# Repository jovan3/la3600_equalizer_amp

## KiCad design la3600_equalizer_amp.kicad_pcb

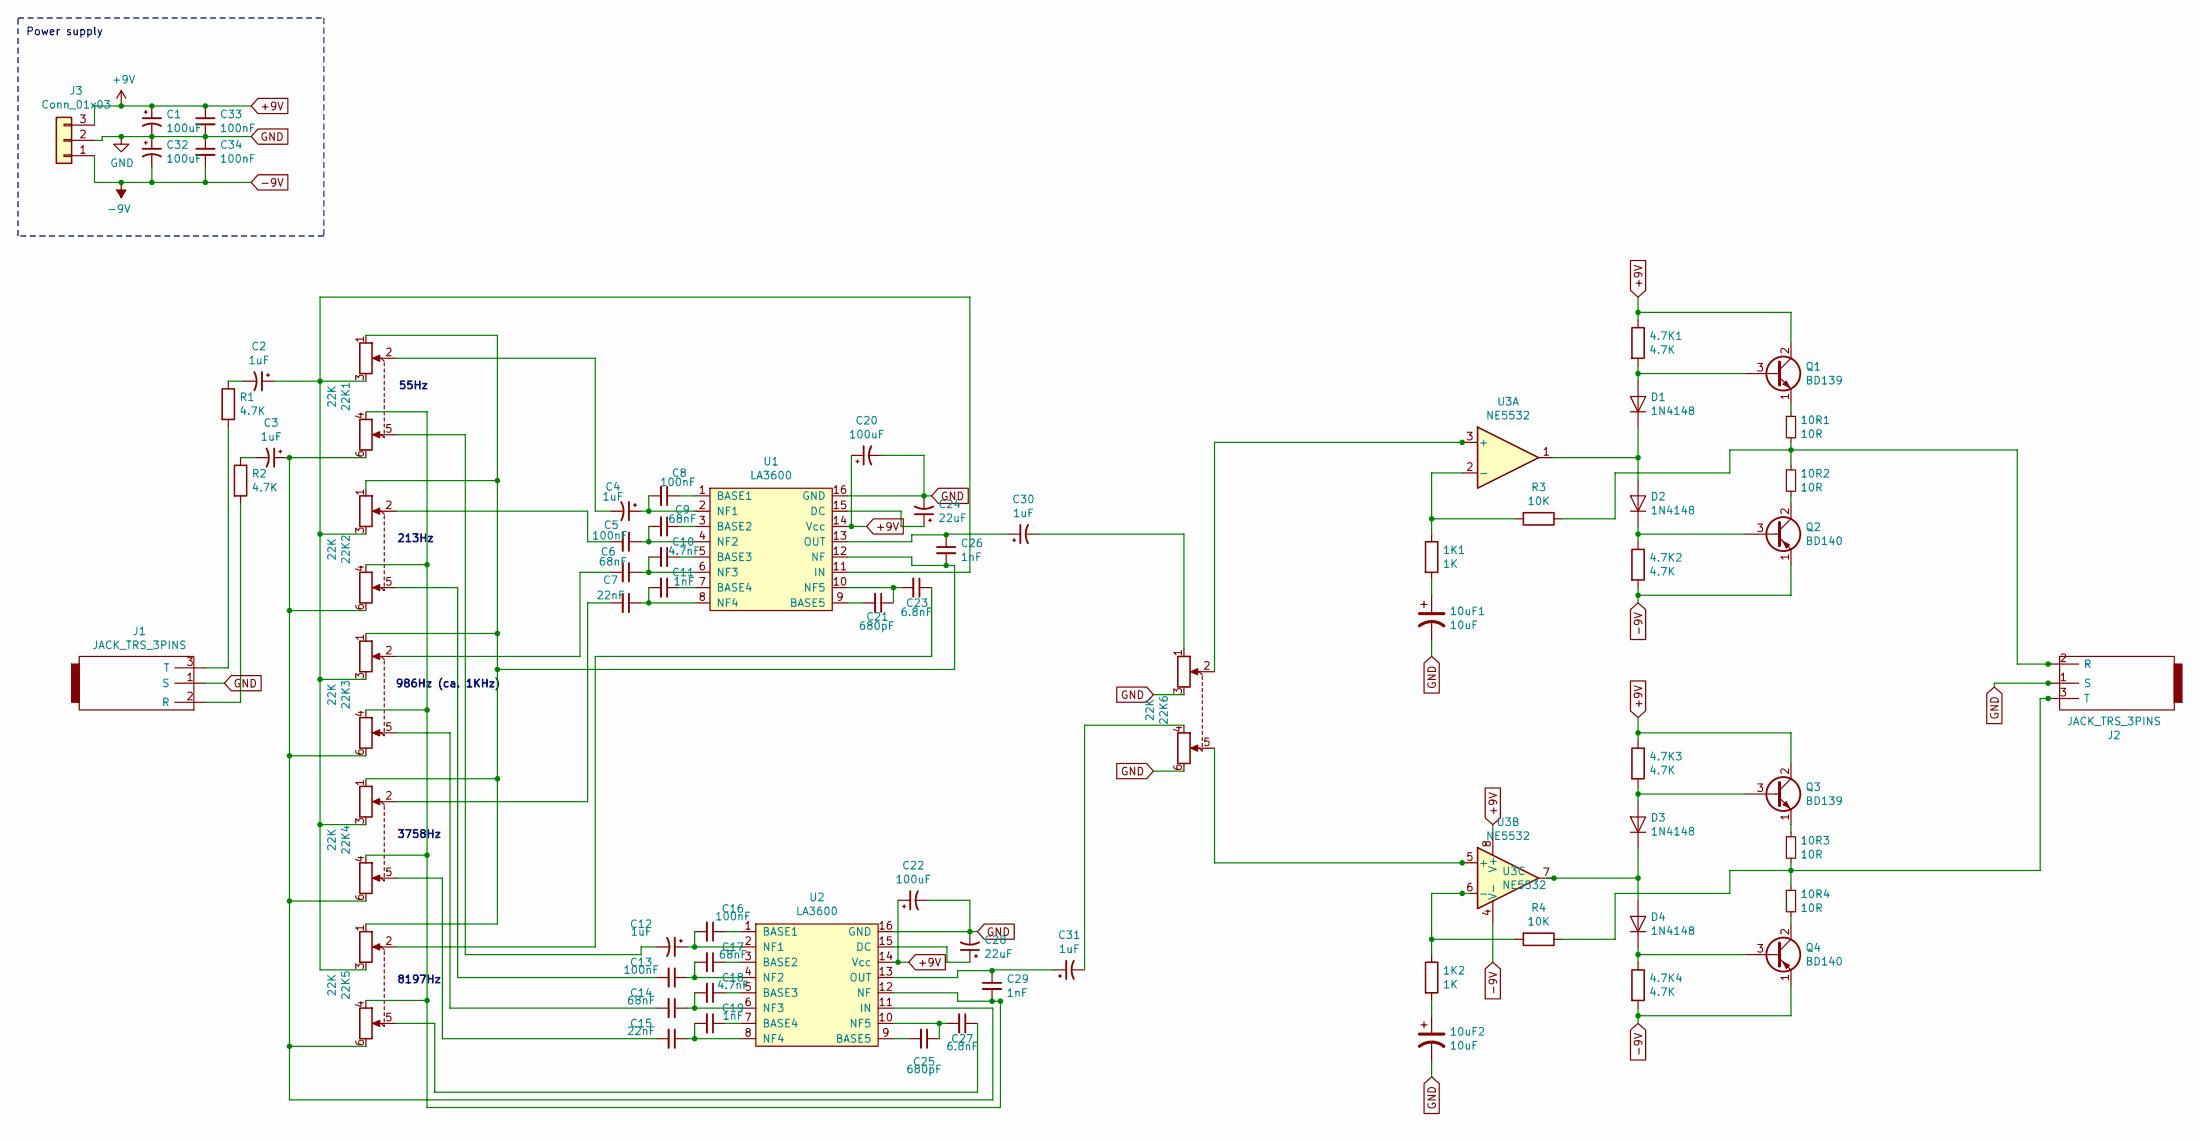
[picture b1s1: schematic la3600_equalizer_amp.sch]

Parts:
1K1, 1K2: 1K; R_Axial_DIN0207_L6.3mm_D2.5mm_P10.16mm_Horizontal
4.7K1, 4.7K2, 4.7K3, 4.7K4: 4.7K; R_Axial_DIN0207_L6.3mm_D2.5mm_P10.16mm_Horizontal
10R1, 10R2, 10R3, 10R4: 10R; R_Axial_DIN0207_L6.3mm_D2.5mm_P10.16mm_Horizontal
10uF1, 10uF2: 10uF; CP_Radial_D5.0mm_P2.50mm
22K1, 22K2, 22K3, 22K4, 22K5, 22K6: 22K; Potentiometer_Alps_RK163_Dual_Horizontal
C1, C20, C22, C32: 100uF; CP_Radial_D5.0mm_P2.50mm
C2, C3, C4, C12, C30, C31: 1uF; CP_Radial_D5.0mm_P2.50mm
C5, C8, C13, C16, C33, C34: 100nF; C_Disc_D3.0mm_W2.0mm_P2.50mm
C6, C9, C14, C17: 68nF; C_Disc_D3.0mm_W2.0mm_P2.50mm
C7, C15: 22nF; C_Disc_D3.0mm_W2.0mm_P2.50mm
C10, C18: 4.7nF; C_Disc_D3.0mm_W2.0mm_P2.50mm
C11, C19, C26, C29: 1nF; C_Disc_D3.0mm_W2.0mm_P2.50mm
C21, C25: 680pF; C_Disc_D3.0mm_W2.0mm_P2.50mm
C23, C27: 6.8nF; C_Disc_D3.0mm_W2.0mm_P2.50mm
C24, C28: 22uF; CP_Radial_D5.0mm_P2.50mm
D1, D2, D3, D4: 1N4148; D_DO-35_SOD27_P7.62mm_Horizontal
J1, J2: JACK_TRS_3PINS; 3.5mm_stereo_TRS_jack
J3: Conn_01x03; PinHeader_1x03_P2.54mm_Vertical
Q1, Q3: BD139; TO-126-3_Vertical
Q2, Q4: BD140; TO-126-3_Vertical
R1, R2: 4.7K; R_Axial_DIN0207_L6.3mm_D2.5mm_P10.16mm_Horizontal
R3, R4: 10K; R_Axial_DIN0207_L6.3mm_D2.5mm_P10.16mm_Horizontal
U1, U2: LA3600; DIP-16_W7.62mm_Socket
U3: NE5532; DIP-8_W7.62mm_Socket

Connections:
+9V: 4.7K1.1, 4.7K3.1, C1.1, C20.1, C22.1, C33.1, J3.3, Q1.2 (C), Q3.2 (C), U1.14 (Vcc), U2.14 (Vcc), U3.8 (V+)
-9V: 4.7K2.2, 4.7K4.2, C32.2, C34.2, J3.1, Q2.1 (E), Q4.1 (E), U3.4 (V-)
GND: 10uF1.2, 10uF2.2, 22K6.3, 22K6.6, C1.2, C20.2, C22.2, C24.2, C28.2, C32.1, C33.2, C34.1, J1.1 (S), J2.1 (S), J3.2, U1.16 (GND), U2.16 (GND)
unnamed: 1K1.1, R3.2, U3.2 (-)
unnamed: 1K2.1, R4.2, U3.6 (-)
unnamed: 4.7K1.2, D1.2 (A), Q1.3 (B)
unnamed: 4.7K2.1, D2.1 (K), Q2.3 (B)
unnamed: 4.7K3.2, D3.2 (A), Q3.3 (B)
unnamed: 4.7K4.1, D4.1 (K), Q4.3 (B)
unnamed: 10R1.1, Q1.1 (E)
unnamed: 10R1.2, 10R2.1, J2.2 (R), R3.1
unnamed: 10R2.2, Q2.2 (C)
unnamed: 10R3.1, Q3.1 (E)
unnamed: 10R3.2, 10R4.1, J2.3 (T), R4.1
unnamed: 10R4.2, Q4.2 (C)
unnamed: 1K1.2, 10uF1.1
unnamed: 1K2.2, 10uF2.1
unnamed: 22K1.1, 22K2.1, 22K3.1, 22K4.1, 22K5.1, C26.2, U1.12 (NF)
unnamed: 22K1.2, C4.2
unnamed: 22K1.3, 22K2.3, 22K3.3, 22K4.3, 22K5.3, C2.1, U1.11 (IN)
unnamed: 22K1.4, 22K2.4, 22K3.4, 22K4.4, 22K5.4, C29.2, U2.12 (NF)
unnamed: 22K1.5, C12.2
unnamed: 22K1.6, 22K2.6, 22K3.6, 22K4.6, 22K5.6, C3.1, U2.11 (IN)
unnamed: 22K2.2, C5.2
unnamed: 22K2.5, C13.2
unnamed: 22K3.2, C6.2
unnamed: 22K3.5, C14.2
unnamed: 22K4.2, C7.2
unnamed: 22K4.5, C15.2
unnamed: 22K5.2, C23.1
unnamed: 22K5.5, C27.1
unnamed: 22K6.1, C30.2
unnamed: 22K6.2, U3.3 (+)
unnamed: 22K6.4, C31.2
unnamed: 22K6.5, U3.5 (+)
unnamed: C2.2, R1.1
unnamed: C3.2, R2.1
unnamed: C4.1, C8.2, U1.2 (NF1)
unnamed: C5.1, C9.2, U1.4 (NF2)
unnamed: C8.1, U1.1 (BASE1)
unnamed: C9.1, U1.3 (BASE2)
unnamed: C10.1, U1.5 (BASE3)
unnamed: C6.1, C10.2, U1.6 (NF3)
unnamed: C11.1, U1.7 (BASE4)
unnamed: C7.1, C11.2, U1.8 (NF4)
unnamed: C12.1, C16.2, U2.2 (NF1)
unnamed: C13.1, C17.2, U2.4 (NF2)
unnamed: C14.1, C18.2, U2.6 (NF3)
unnamed: C15.1, C19.2, U2.8 (NF4)
unnamed: C16.1, U2.1 (BASE1)
unnamed: C17.1, U2.3 (BASE2)
unnamed: C18.1, U2.5 (BASE3)
unnamed: C19.1, U2.7 (BASE4)
unnamed: C21.1, C23.2, U1.10 (NF5)
unnamed: C21.2, U1.9 (BASE5)
unnamed: C24.1, U1.15 (DC)
unnamed: C25.1, C27.2, U2.10 (NF5)
unnamed: C25.2, U2.9 (BASE5)
unnamed: C26.1, C30.1, U1.13 (OUT)
unnamed: C28.1, U2.15 (DC)
unnamed: C29.1, C31.1, U2.13 (OUT)
unnamed: D1.1 (K), D2.2 (A), U3.1
unnamed: D3.1 (K), D4.2 (A), U3.7
unnamed: J1.2 (R), R2.2
unnamed: J1.3 (T), R1.2

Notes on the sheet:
55Hz
213Hz
986Hz (ca. 1KHz)
3758Hz
8197Hz
Power supply

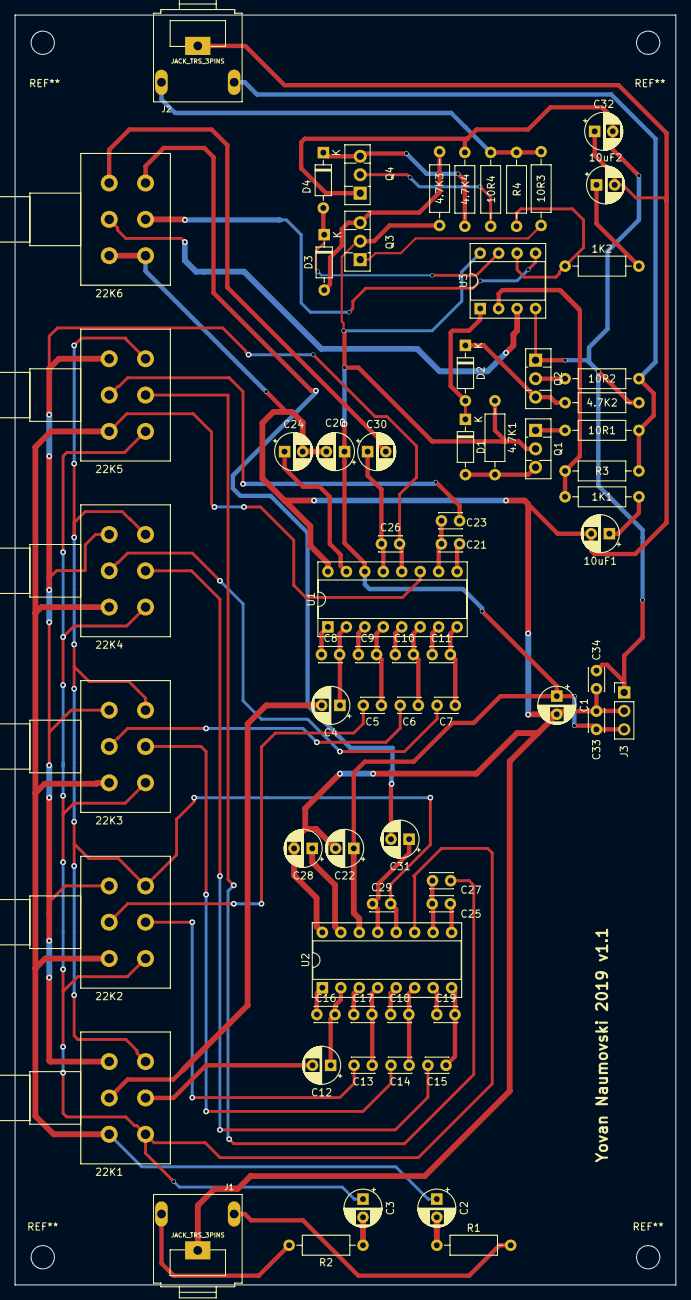
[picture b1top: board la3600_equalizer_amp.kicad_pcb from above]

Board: 2 copper layers, 90.9 x 174.8 mm, 70 parts (0 on the bottom side), 65 nets.

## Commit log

2018-08-21 rename project files (lm -> la oops). add some values to components in Eeschema
2018-08-21 add usb b type connector for powering the device. assign footprints
2018-08-23 initial pcb layout
2018-08-23 some more pcb layout work
2018-08-23 finish pcb layout
2018-09-09 rotate PCB + generate new gerber and excellon files
2019-01-23 kicad 5 modifications
2019-01-24 replace the audio amplifier part of the circuit with a new one based on NE5532 and BD139/BD140 output stage
2019-01-24 add pcb mounting holes
2019-01-24 remove gerber and excellon files
2019-01-24 igrnore .zip files
2019-01-24 add proper mounting holes (M3)
